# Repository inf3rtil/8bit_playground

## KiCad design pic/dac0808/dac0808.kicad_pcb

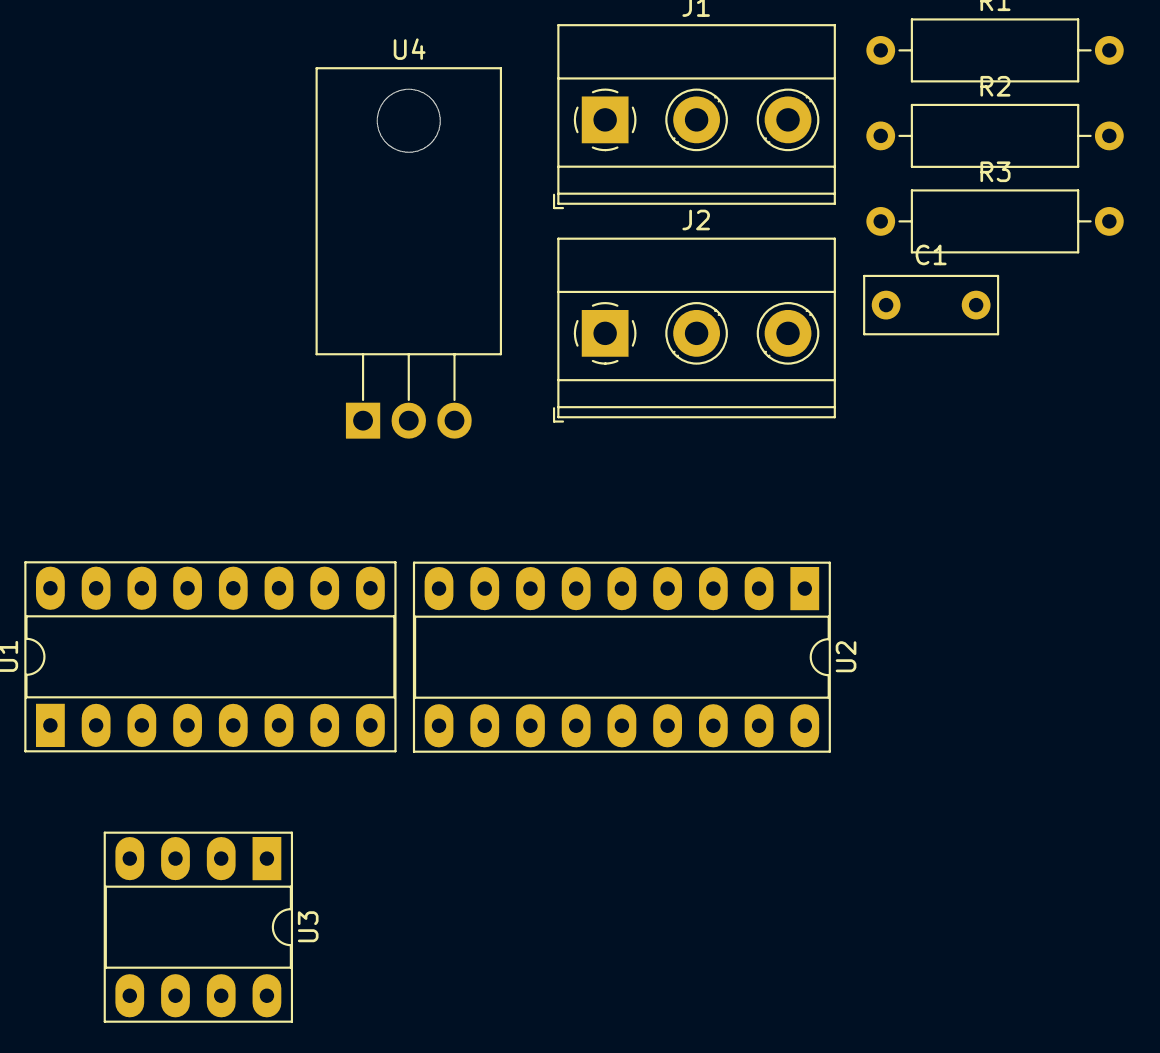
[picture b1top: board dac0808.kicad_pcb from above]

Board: 2 copper layers, 10 parts (0 on the bottom side), 16 nets, no tracks yet.

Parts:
C1: C; C_Rect_L7.2mm_W3.0mm_P5.00mm_FKS2_FKP2_MKS2_MKP2
J1, J2: Conn_01x03_Socket; TerminalBlock_Phoenix_MKDS-1,5-3-5.08_1x03_P5.08mm_Horizont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
R1, R2, R3: R; R_Axial_DIN0309_L9.0mm_D3.2mm_P12.70mm_Horizontal
U1: DAC0808_DIP; DIP-16_W7.62mm_Socket_LongPads
U2: PIC16F648A-IP; DIP-18_W7.62mm_Socket_LongPads
U3: LM741; DIP-8_W7.62mm_Socket_LongPads
U4: LM7805_TO220; TO-220-3_Horizontal_TabDown

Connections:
-15V: C1.2, U1.3 (VEE), U3.4 (V-)
/BIT0: U1.12 (A1), U2.6 (RB0/INT)
/BIT1: U1.11 (A2), U2.7 (RB1/RX/DT)
/BIT2: U1.10 (A3), U2.8 (RB2/TX/CK)
/BIT3: U1.9 (A4), U2.9 (RB3/CCP1)
/BIT4: U1.8 (A5), U2.10 (RB4/PGM)
/BIT5: U1.7 (A6), U2.11 (RB5)
/BIT6: U1.6 (A7), U2.12 (RB6/T1OSC0/T1CKI/PGC)
/BIT7: U1.5 (A8), U2.13 (RB7/T1OSI/PGD)
GNDREF: R2.2, U1.2 (GND), U2.5 (VSS), U4.2 (GND)
unnamed: R2.1, R3.2, U3.6
unnamed: C1.1, U1.16 (COMPEN)
unnamed: R3.1, U1.4 (I0), U3.2 (-)
unnamed: R1.1, U1.15 (VREF-)
unnamed: R1.2, U3.3 (+)
VCC: U1.13 (VCC), U2.14 (VDD)

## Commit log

2024-08-19 Makefile for AVR
2024-08-19 update Makefile
2024-08-19 asm blink
2024-09-23 blink avr
2024-09-23 DAC0808 with PIC16
2024-10-21 first version of waveController
2024-10-21 first version of wave generator
2024-10-22 add template for avr
2024-10-22 WIP: wave generator
2024-10-25 first version for atmega328
2024-10-26 wave tracer with delay
